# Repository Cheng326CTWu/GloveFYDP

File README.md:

# GloveFYDP

## Environment requirements
* System Workbench for STM32
* A serial terminal like CoolTerm, Putty, TeraTerm
* STMCubeMX

## Hardware requirements
* STM Nucleo board.
* Micro usb type B cable for the Nucleo.
* Peripherals used so far include the Sparkfun LSM9DS1 breakout, and the Adafruit TCA TCA9548A breakout.

## Source files
Most files were generated automatically by STMCubeMX. Src/ contains the actual source files we work on.
The STMCube project is the .ioc file.

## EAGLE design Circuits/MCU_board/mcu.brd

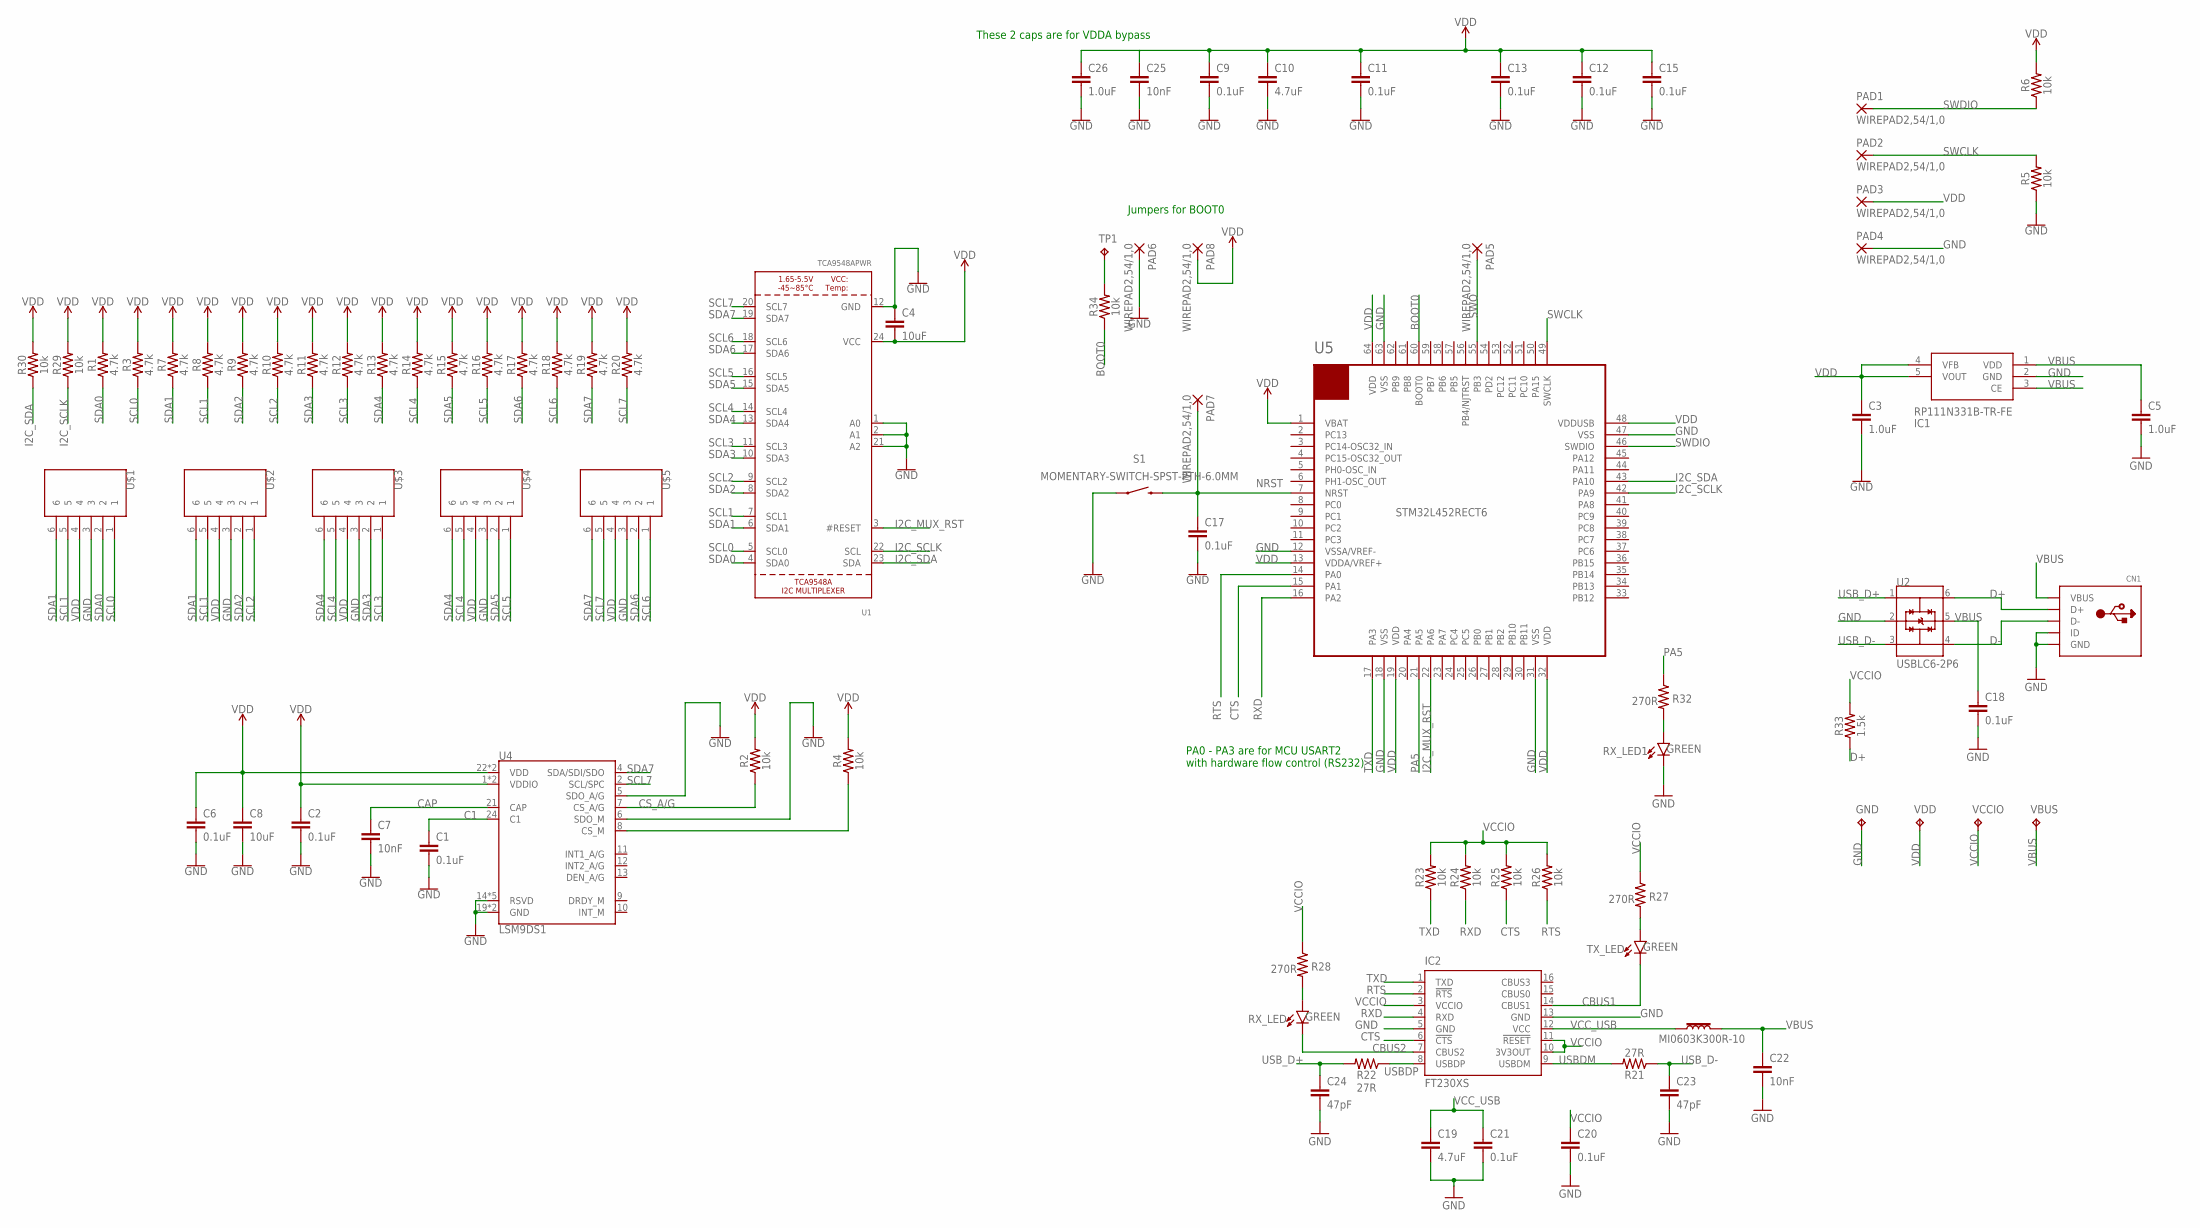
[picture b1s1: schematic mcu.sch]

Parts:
C1, C2, C6, C9, C11, C12, C13, C15, C17, C18, C20, C21: 0.1uF; 0603
C3, C5, C26: 1.0uF; 0603
C4, C8: 10uF; 0603
C7, C22, C25: 10nF; 0603
C10, C19: 4.7uF; 0603
C23, C24: 47pF; 0603
CN1: USBMINIB; USB-MINIB
GND: TPB2,54; B2,54
IC1: RP111N331B-TR-FE; SOT95P280X120-5N
IC2: FT230XS; SSOP16
MI0603K300R-10: 30Ω/1.8A; 0603
PAD1, PAD2, PAD3, PAD4, PAD5, PAD6, PAD7, PAD8: WIREPAD2,54/1,0; 2,54/1,0
R1, R3, R7, R8, R9, R10, R11, R12, R13, R14, R15, R16, R17, R18, R19, R20: 4.7k; 0603
R2, R4, R5, R6, R23, R24, R25, R26, R29, R30, R34: 10k; 0603
R21, R22: 27R; 0603
R27, R28, R32: 270R; 0603
R33: 1.5k; 0603
RX_LED, RX_LED1: GREEN; LED-0603
S1: MOMENTARY-SWITCH-SPST-PTH-6.0MM; TACTILE_SWITCH_PTH_6.0MM
TP1: TPB1,27; B1,27
TX_LED: GREEN; LED-0603
U1: TCA9548APWR; TSSOP24
U2: USBLC6-2P6; SOT50P160X60-6N
U4: LSM9DS1; LGA-24-3.5X3
U5: STM32L452RECT6; LQFP-64
U$1, U$2, U$3, U$4, U$5: MOLEX_522070633; MOLEX6_1MM
VBUS: TPB2,54; B2,54
VCCIO: TPB2,54; B2,54
VDD: TPB2,54; B2,54

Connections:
BOOT0: R34.1, U5.60 (BOOT0)
C1: C1.1, U4.24 (C1)
CAP: C7.1, U4.21 (CAP)
CBUS1: IC2.14 (CBUS1), TX_LED.C
CBUS2: IC2.7 (CBUS2), RX_LED.C
CS_A/G: R2.1, U4.7 (CS_A/G)
CS_M: R4.1, U4.8 (CS_M)
CTS: IC2.6 (!CTS), R25.1, U5.15 (PA1)
D+: CN1.D+, R33.1, U2.6 (I/O1_2)
D-: CN1.D-, U2.4 (I/O2_2)
GND: C1.2, C2.2, C3.2, C4.1, C5.2, C6.2, C7.2, C8.2, C9.2, C10.2, C11.2, C12.2, C13.2, C15.2, C17.2, C18.2, C19.2, C20.2, C21.2, C22.2, C23.2, C24.2, C25.2, C26.2, CN1.GND, CN1.ID, GND.TP, IC1.2 (GND), IC2.5 (GND), IC2.13 (GND), PAD4.1, PAD6.1, R5.1, RX_LED1.C, S1.1, U1.1 (A0), U1.2 (A1), U1.12 (GND), U1.21 (A2), U2.2 (GND), U4.5 (SDO_A/G), U4.6 (SDO_M), U4.14 (RSVD), U4.15 (RSVD), U4.16 (RSVD), U4.17 (RSVD), U4.18 (RSVD), U4.19 (GND), U4.20 (GND), U5.12 (VSSA/VREF-), U5.18 (VSS), U5.31 (VSS), U5.47 (VSS), U5.63 (VSS), U$1.3, U$2.3, U$3.3, U$4.3, U$5.3
I2C_MUX_RST: U1.3 (#RESET), U5.22 (PA6)
I2C_SCLK: R29.1, U1.22 (SCL), U5.42 (PA9)
I2C_SDA: R30.1, U1.23 (SDA), U5.43 (PA10)
unnamed: R27.2, TX_LED.A
unnamed: R28.2, RX_LED.A
unnamed: R32.2, RX_LED1.A
unnamed: R34.2, TP1.TP
NRST: C17.1, PAD7.1, S1.3 (2), U5.7 (NRST)
PA5: R32.1, U5.21 (PA5)
RTS: IC2.2 (!RTS), R26.1, U5.14 (PA0)
RXD: IC2.4 (RXD), R24.1, U5.16 (PA2)
SCL0: R3.1, U1.5 (SCL0), U$1.1
SCL1: R8.1, U1.7 (SCL1), U$1.5, U$2.5
SCL2: R10.1, U1.9 (SCL2), U$2.1
SCL3: R12.1, U1.11 (SCL3), U$3.1
SCL4: R14.1, U1.14 (SCL4), U$3.5, U$4.5
SCL5: R16.1, U1.16 (SCL5), U$4.1
SCL6: R18.1, U1.18 (SCL6), U$5.1
SCL7: R20.1, U1.20 (SCL7), U4.2 (SCL/SPC), U$5.5
SDA0: R1.1, U1.4 (SDA0), U$1.2
SDA1: R7.1, U1.6 (SDA1), U$1.6, U$2.6
SDA2: R9.1, U1.8 (SDA2), U$2.2
SDA3: R11.1, U1.10 (SDA3), U$3.2
SDA4: R13.1, U1.13 (SDA4), U$3.6, U$4.6
SDA5: R15.1, U1.15 (SDA5), U$4.2
SDA6: R17.1, U1.17 (SDA6), U$5.2
SDA7: R19.1, U1.19 (SDA7), U4.4 (SDA/SDI/SDO), U$5.6
SWCLK: PAD2.1, R5.2, U5.49 (SWCLK)
SWDIO: PAD1.1, R6.1, U5.46 (SWDIO)
SWO: PAD5.1, U5.55 (PB3)
TXD: IC2.1 (TXD), R23.1, U5.17 (PA3)
USBDM: IC2.9 (USBDM), R21.2
USBDP: IC2.8 (USBDP), R22.1
USB_D+: C24.1, R22.2, U2.1 (I/O1_1)
USB_D-: C23.1, R21.1, U2.3 (I/O2_1)
VBUS: C5.1, C18.1, C22.1, CN1.VBUS, IC1.1 (VDD), IC1.3 (CE), MI0603K300R-10.2, U2.5 (VBUS), VBUS.TP
VCCIO: C20.1, IC2.3 (VCCIO), IC2.10 (3V3OUT), IC2.11 (!RESET), R23.2, R24.2, R25.2, R26.2, R27.1, R28.1, R33.2, VCCIO.TP
VCC_USB: C19.1, C21.1, IC2.12 (VCC), MI0603K300R-10.1
VDD: C2.1, C3.1, C4.2, C6.1, C8.1, C9.1, C10.1, C11.1, C12.1, C13.1, C15.1, C25.1, C26.1, IC1.4 (VFB), IC1.5 (VOUT), PAD3.1, PAD8.1, R1.2, R2.2, R3.2, R4.2, R6.2, R7.2, R8.2, R9.2, R10.2, R11.2, R12.2, R13.2, R14.2, R15.2, R16.2, R17.2, R18.2, R19.2, R20.2, R29.2, R30.2, U1.24 (VCC), U4.1 (VDDIO), U4.3 (VDDIO), U4.22 (VDD), U4.23 (VDD), U5.1 (VBAT), U5.13 (VDDA/VREF+), U5.19 (VDD), U5.32 (VDD), U5.48 (VDDUSB), U5.64 (VDD), U$1.4, U$2.4, U$3.4, U$4.4, U$5.4, VDD.TP

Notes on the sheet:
PA0 - PA3 are for MCU USART2 with hardware flow control (RS232)
These 2 caps are for VDDA bypass
Jumpers for BOOT0

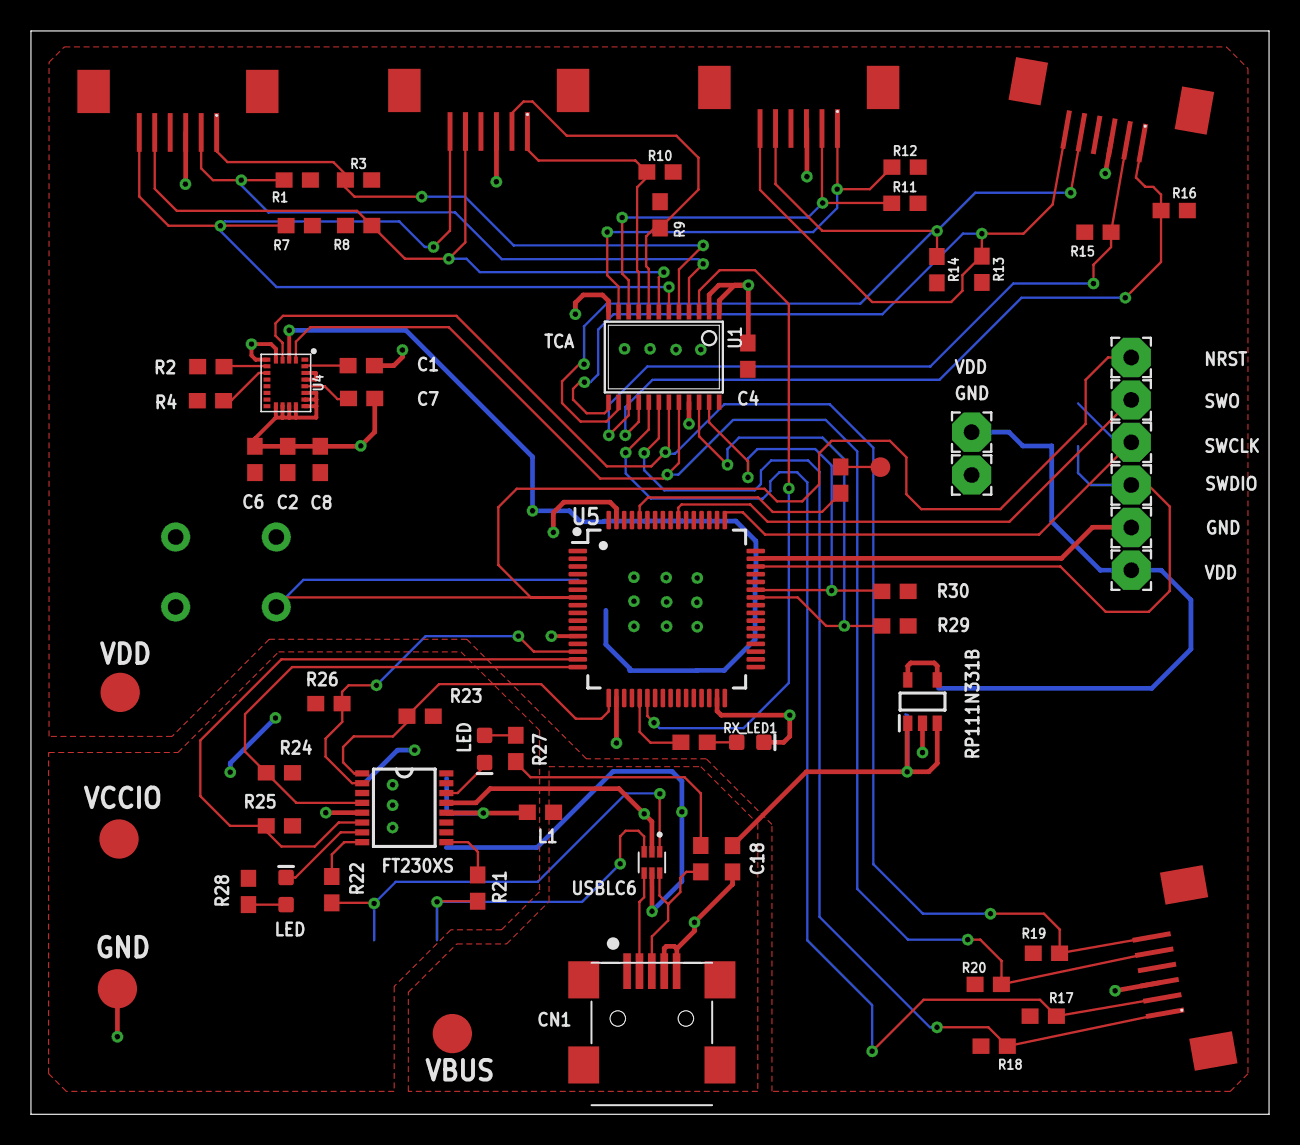
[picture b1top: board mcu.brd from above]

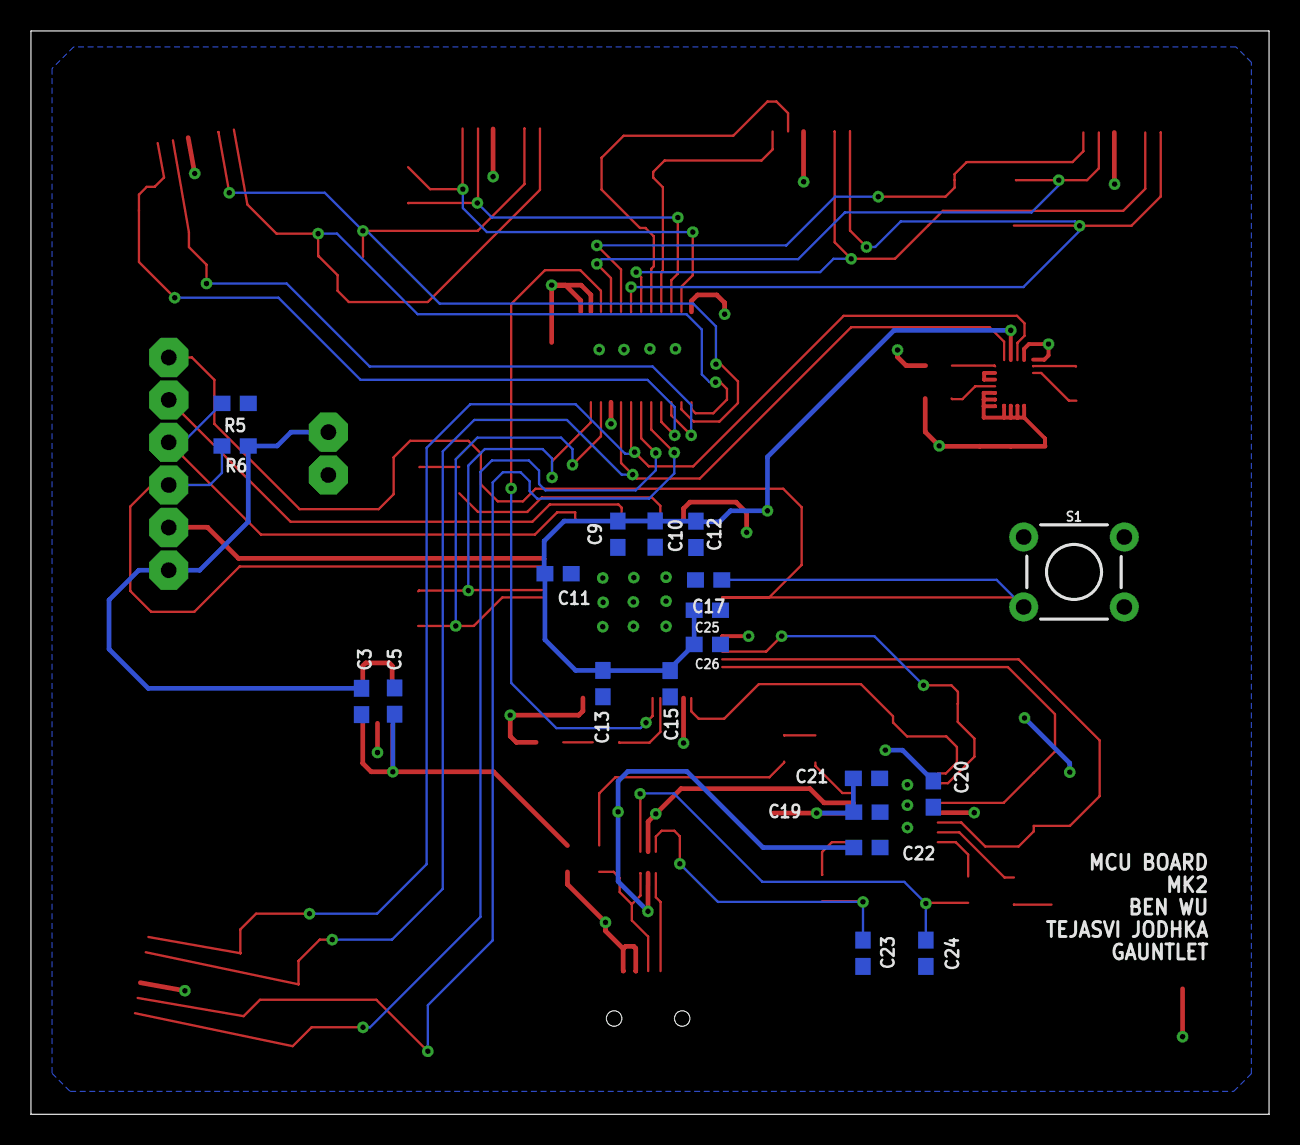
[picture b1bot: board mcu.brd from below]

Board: 2 copper layers, 80.0 x 70.0 mm, 87 parts (20 on the bottom side), 50 nets.

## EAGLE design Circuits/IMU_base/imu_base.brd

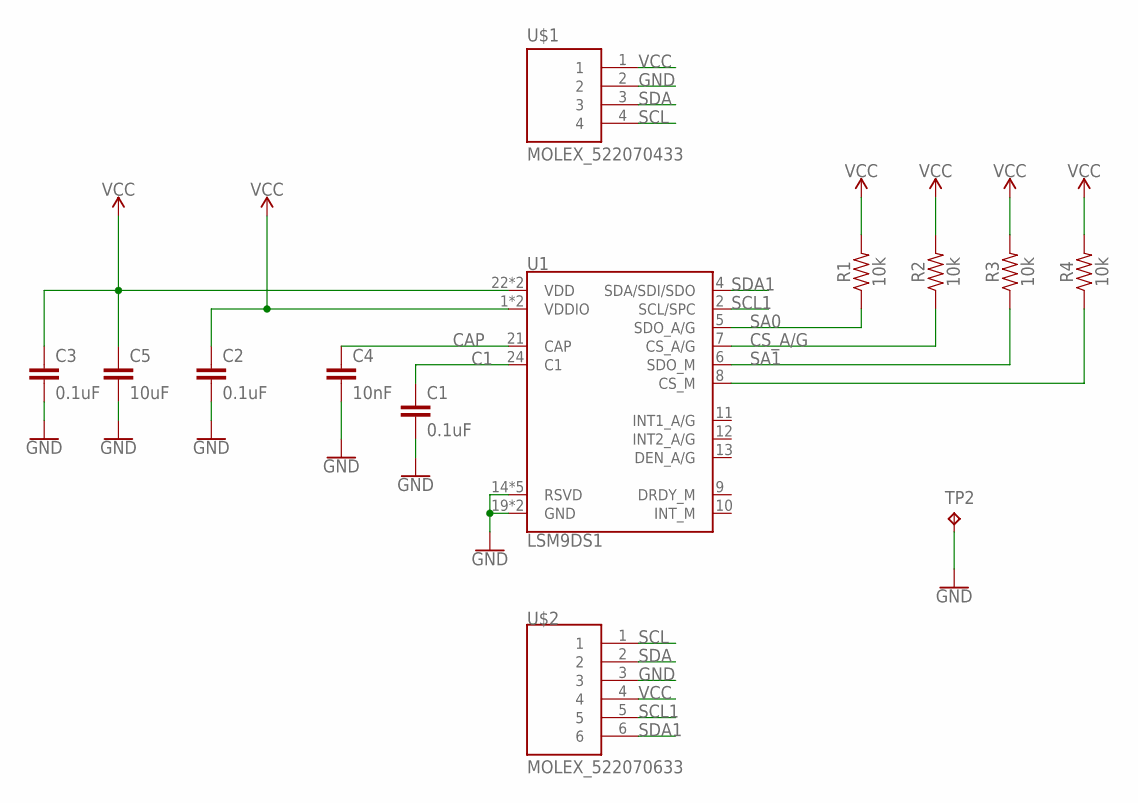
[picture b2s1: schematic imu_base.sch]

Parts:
C1, C2, C3: 0.1uF; 0603
C4: 10nF; 0603
C5: 10uF; 0603
R1, R2, R3, R4: 10k; 0603
TP2: TPB2,54; B2,54
U1: LSM9DS1; LGA-24-3.5X3
U$1: MOLEX_522070433; MOLEX4_1MM
U$2: MOLEX_522070633; MOLEX6_1MM

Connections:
C1: C1.1, U1.24 (C1)
CAP: C4.1, U1.21 (CAP)
CS_A/G: R2.1, U1.7 (CS_A/G)
CS_M: R4.1, U1.8 (CS_M)
GND: C1.2, C2.2, C3.2, C4.2, C5.2, TP2.TP, U1.14 (RSVD), U1.15 (RSVD), U1.16 (RSVD), U1.17 (RSVD), U1.18 (RSVD), U1.19 (GND), U1.20 (GND), U$1.2, U$2.3
SA0: R1.1, U1.5 (SDO_A/G)
SA1: R3.1, U1.6 (SDO_M)
SCL: U$1.4, U$2.1
SCL1: U1.2 (SCL/SPC), U$2.5
SDA: U$1.3, U$2.2
SDA1: U1.4 (SDA/SDI/SDO), U$2.6
VCC: C2.1, C3.1, C5.1, R1.2, R2.2, R3.2, R4.2, U1.1 (VDDIO), U1.3 (VDDIO), U1.22 (VDD), U1.23 (VDD), U$1.1, U$2.4

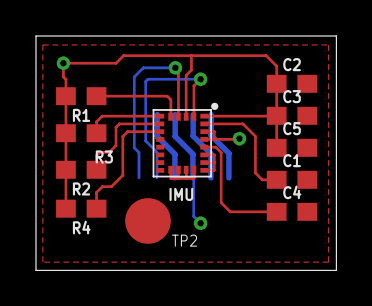
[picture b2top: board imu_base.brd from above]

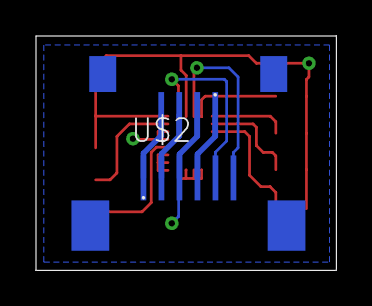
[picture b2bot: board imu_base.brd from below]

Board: 2 copper layers, 16.7 x 13.0 mm, 13 parts (2 on the bottom side), 12 nets.

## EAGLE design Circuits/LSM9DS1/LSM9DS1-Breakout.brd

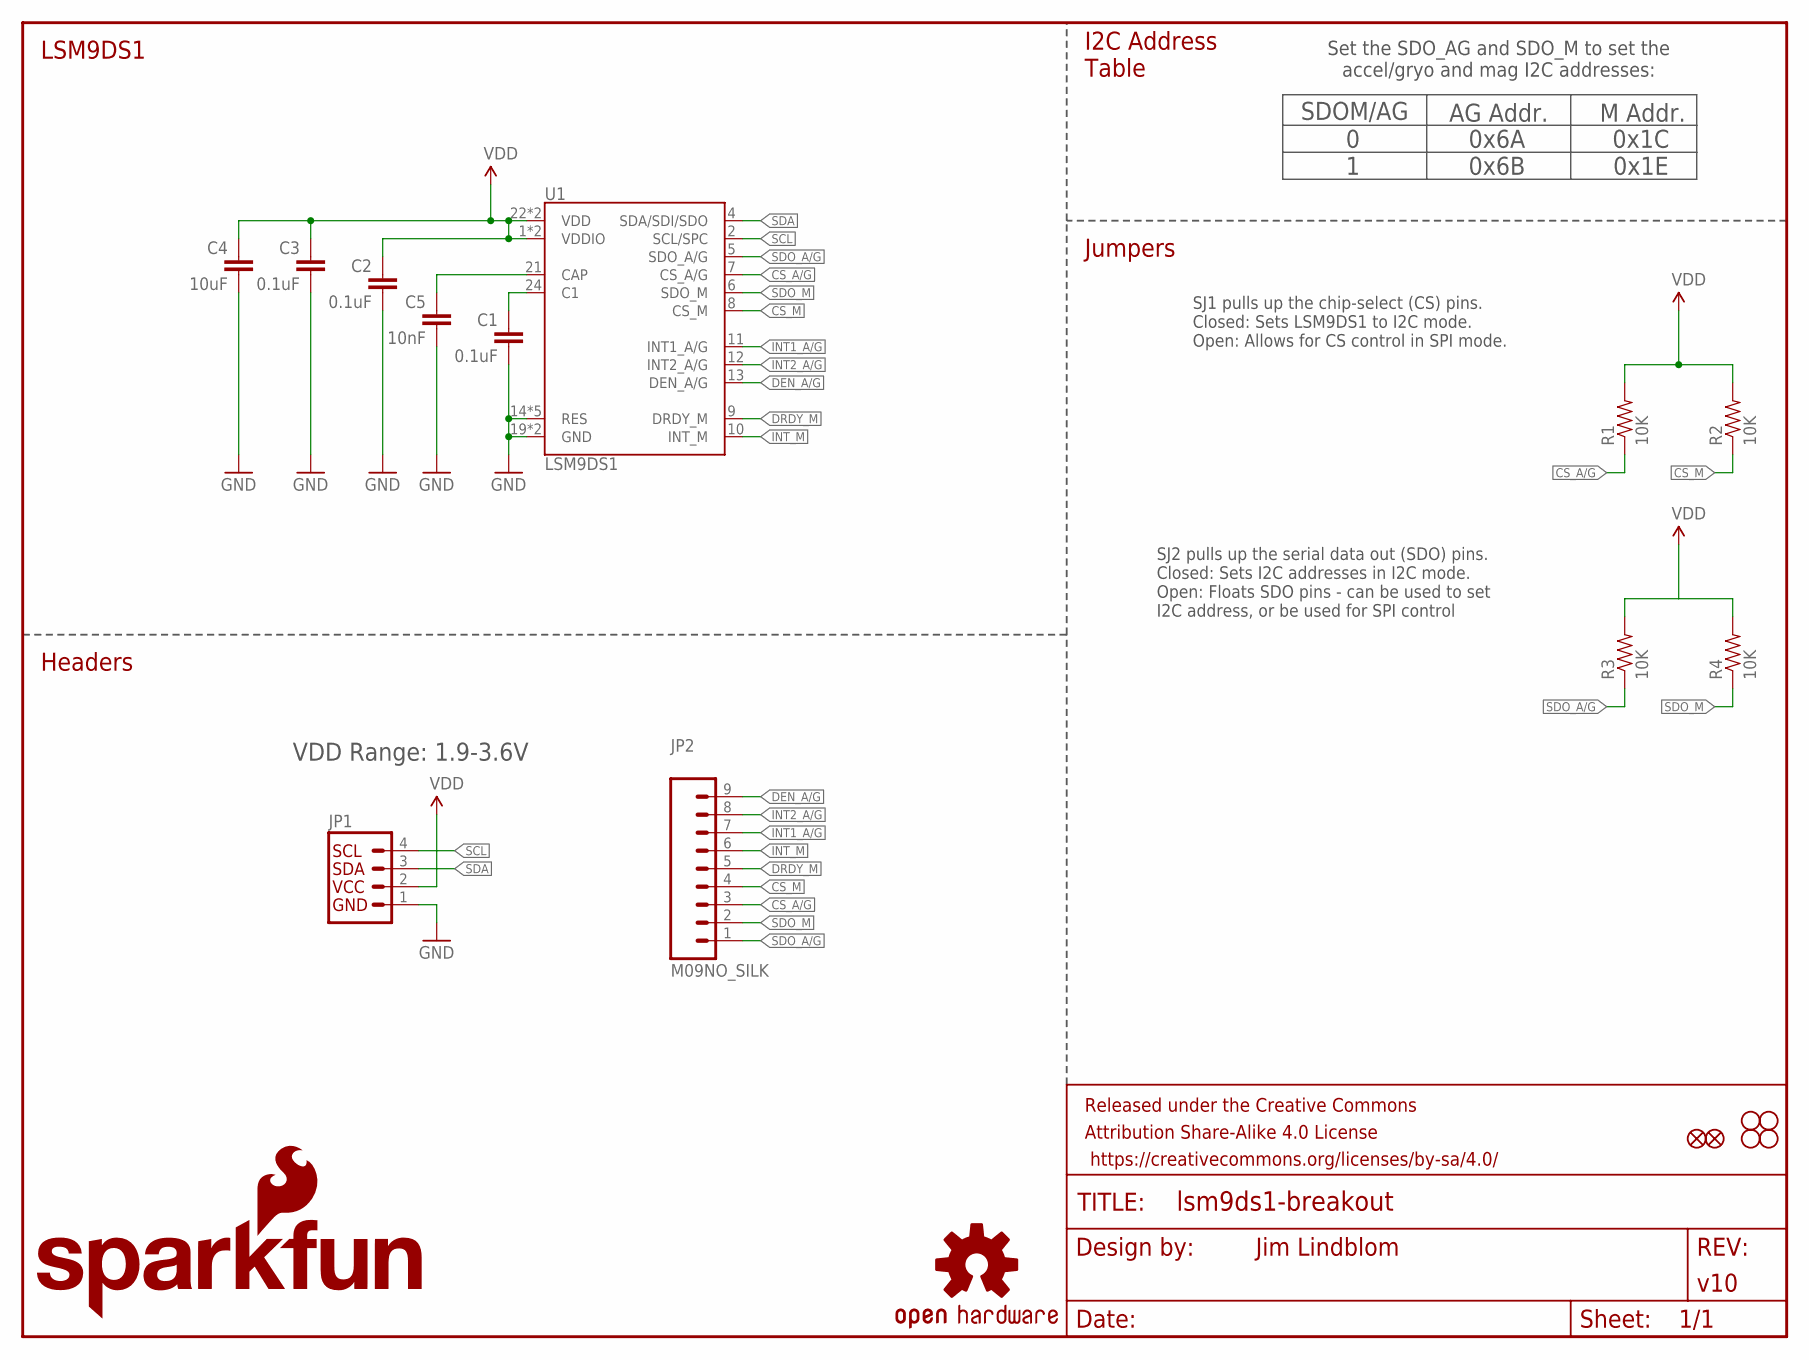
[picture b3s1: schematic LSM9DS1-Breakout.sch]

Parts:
C1, C2, C3: 0.1uF; 0603-CAP
C4: 10uF; 0603-CAP
C5: 10nF; 0603-CAP
FID1, FID2: FIDUCIAL1X2; FIDUCIAL-1X2
FRAME1: FRAME-LETTER; CREATIVE_COMMONS
JP1: I2C_STANDARD_NO_SILK; 1X04_NO_SILK
JP2: M09NO_SILK; 1X09_NO_SILK
LOGO1: SFE_LOGO_NAME.1_INCH; SFE_LOGO_NAME_.1
LOGO2: SFE_LOGO_FLAME.2_INCH; SFE_LOGO_FLAME_.2
LOGO3: OSHW-LOGOS; OSHW-LOGO-S
R1, R2, R3, R4: 10K; 0603-RES
STANDOFF1, STANDOFF2, STANDOFF3, STANDOFF4: STAND-OFF
U1: LSM9DS1; LGA24-8X4

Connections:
C1: C1.1, U1.24 (C1)
CAP: C5.1, U1.21 (CAP)
CS_A/G: JP2.3, R1.1, U1.7 (CS_A/G)
CS_M: JP2.4, R2.1, U1.8 (CS_M)
DEN_A/G: JP2.9, U1.13 (DEN_A/G)
DRDY_M: JP2.5, U1.9 (DRDY_M)
GND: C1.2, C2.2, C3.2, C4.2, C5.2, JP1.1, U1.14 (RES), U1.15 (RES), U1.16 (RES), U1.17 (RES), U1.18 (RES), U1.19 (GND), U1.20 (GND)
INT1_A/G: JP2.7, U1.11 (INT1_A/G)
INT2_A/G: JP2.8, U1.12 (INT2_A/G)
INT_M: JP2.6, U1.10 (INT_M)
SCL: JP1.4, U1.2 (SCL/SPC)
SDA: JP1.3, U1.4 (SDA/SDI/SDO)
SDO_A/G: JP2.1, R3.1, U1.5 (SDO_A/G)
SDO_M: JP2.2, R4.1, U1.6 (SDO_M)
VDD: C2.1, C3.1, C4.1, JP1.2, R1.2, R2.2, R3.2, R4.2, U1.1 (VDDIO), U1.3 (VDDIO), U1.22 (VDD), U1.23 (VDD)

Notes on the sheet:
SDOM/AG
0x1C 0x1E
AG Addr.
0 1
M Addr.
0x6A 0x6B
Set the SDO_AG and SDO_M to set the accel/gryo and mag I2C addresses:
SJ1 pulls up the chip-select (CS) pins. Closed: Sets LSM9DS1 to I2C mode. Open: Allows for CS control in SPI mode.
SJ2 pulls up the serial data out (SDO) pins. Closed: Sets I2C addresses in I2C mode. Open: Floats SDO pins - can be used to set I2C address, or be used for SPI control
Jumpers
I2C Address Table
LSM9DS1
Headers
VDD Range: 1.9-3.6V

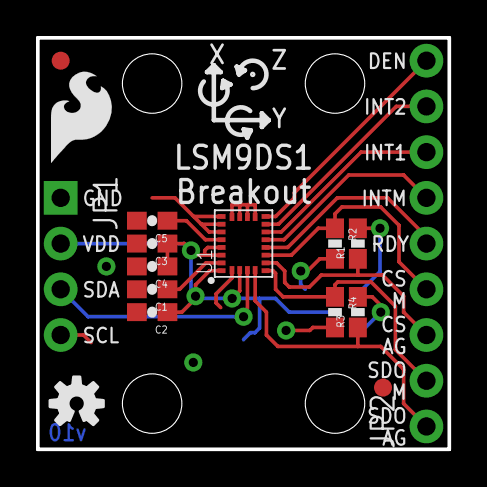
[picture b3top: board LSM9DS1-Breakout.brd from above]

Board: 2 copper layers, 22.9 x 22.9 mm, 22 parts (1 on the bottom side), 15 nets.

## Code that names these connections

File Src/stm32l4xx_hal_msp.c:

/* USER CODE BEGIN Header */
/**
  ******************************************************************************
  * File Name          : stm32l4xx_hal_msp.c
  * Description        : This file provides code for the MSP Initialization 
  *                      and de-Initialization codes.
  ******************************************************************************
  * @attention
  *
  * <h2><center>&copy; Copyright (c) 2019 STMicroelectronics.
  * All rights reserved.</center></h2>
  *
  * This software component is licensed by ST under BSD 3-Clause license,
  * the "License"; You may not use this file except in compliance with the
  * License. You may obtain a copy of the License at:
  *                        opensource.org/licenses/BSD-3-Clause
  *
  ******************************************************************************
  */
/* USER CODE END Header */

/* Includes ------------------------------------------------------------------*/
#include "main.h"
/* USER CODE BEGIN Includes */

/* USER CODE END Includes */
extern DMA_HandleTypeDef hdma_usart2_rx;

extern DMA_HandleTypeDef hdma_usart2_tx;

/* Private typedef -----------------------------------------------------------*/
/* USER CODE BEGIN TD */

/* USER CODE END TD */

/* Private define ------------------------------------------------------------*/
/* USER CODE BEGIN Define */
 
/* USER CODE END Define */

/* Private macro -------------------------------------------------------------*/
/* USER CODE BEGIN Macro */

/* USER CODE END Macro */

/* Private variables ---------------------------------------------------------*/
/* USER CODE BEGIN PV */

/* USER CODE END PV */

/* Private function prototypes -----------------------------------------------*/
/* USER CODE BEGIN PFP */

/* USER CODE END PFP */

/* External functions --------------------------------------------------------*/
/* USER CODE BEGIN ExternalFunctions */

/* USER CODE END ExternalFunctions */

/* USER CODE BEGIN 0 */

/* USER CODE END 0 */
/**
  * Initializes the Global MSP.
  */
void HAL_MspInit(void)
{
  /* USER CODE BEGIN MspInit 0 */

  /* USER CODE END MspInit 0 */

  __HAL_RCC_SYSCFG_CLK_ENABLE();
  __HAL_RCC_PWR_CLK_ENABLE();

  /* System interrupt init*/

  /* USER CODE BEGIN MspInit 1 */

  /* USER CODE END MspInit 1 */
}

/**
* @brief I2C MSP Initialization
* This function configures the hardware resources used in this example
* @param hi2c: I2C handle pointer
* @retval None
*/
void HAL_I2C_MspInit(I2C_HandleTypeDef* hi2c)
{
  GPIO_InitTypeDef GPIO_InitStruct = {0};
  if(hi2c->Instance==I2C1)
  {
  /* USER CODE BEGIN I2C1_MspInit 0 */

  /* USER CODE END I2C1_MspInit 0 */
  
    __HAL_RCC_GPIOA_CLK_ENABLE();
    /**I2C1 GPIO Configuration    
    PA9     ------> I2C1_SCL
    PA10     ------> I2C1_SDA 
    */
    GPIO_InitStruct.Pin = GPIO_PIN_9|GPIO_PIN_10;
    GPIO_InitStruct.Mode = GPIO_MODE_AF_OD;
    GPIO_InitStruct.Pull = GPIO_PULLUP;
    GPIO_InitStruct.Speed = GPIO_SPEED_FREQ_VERY_HIGH;
    GPIO_InitStruct.Alternate = GPIO_AF4_I2C1;
    HAL_GPIO_Init(GPIOA, &GPIO_InitStruct);

    /* Peripheral clock enable */
    __HAL_RCC_I2C1_CLK_ENABLE();
  /* USER CODE BEGIN I2C1_MspInit 1 */

  /* USER CODE END I2C1_MspInit 1 */
  }

}

/**
* @brief I2C MSP De-Initialization
* This function freeze the hardware resources used in this example
* @param hi2c: I2C handle pointer
* @retval None
*/
void HAL_I2C_MspDeInit(I2C_HandleTypeDef* hi2c)
{
  if(hi2c->Instance==I2C1)
  {
  /* USER CODE BEGIN I2C1_MspDeInit 0 */

  /* USER CODE END I2C1_MspDeInit 0 */
    /* Peripheral clock disable */
    __HAL_RCC_I2C1_CLK_DISABLE();
  
    /**I2C1 GPIO Configuration    
    PA9     ------> I2C1_SCL
    PA10     ------> I2C1_SDA 
    */
    HAL_GPIO_DeInit(GPIOA, GPIO_PIN_9|GPIO_PIN_10);

  /* USER CODE BEGIN I2C1_MspDeInit 1 */

  /* USER CODE END I2C1_MspDeInit 1 */
  }

}

/**
* @brief UART MSP Initialization
* This function configures the hardware resources used in this example
* @param huart: UART handle pointer
* @retval None
*/
void HAL_UART_MspInit(UART_HandleTypeDef* huart)
{
  GPIO_InitTypeDef GPIO_InitStruct = {0};
  if(huart->Instance==USART2)
  {
  /* USER CODE BEGIN USART2_MspInit 0 */

  /* USER CODE END USART2_MspInit 0 */
    /* Peripheral clock enable */
    __HAL_RCC_USART2_CLK_ENABLE();
  
    __HAL_RCC_GPIOA_CLK_ENABLE();
    /**USART2 GPIO Configuration    
    PA0     ------> USART2_CTS
    PA1     ------> USART2_RTS
    PA2     ------> USART2_TX
    PA3     ------> USART2_RX 
    */
    GPIO_InitStruct.Pin = GPIO_PIN_0|GPIO_PIN_1|USART_TX_Pin|USART_RX_Pin;
    GPIO_InitStruct.Mode = GPIO_MODE_AF_PP;
    GPIO_InitStruct.Pull = GPIO_NOPULL;
    GPIO_InitStruct.Speed = GPIO_SPEED_FREQ_VERY_HIGH;
    GPIO_InitStruct.Alternate = GPIO_AF7_USART2;
    HAL_GPIO_Init(GPIOA, &GPIO_InitStruct);

    /* USART2 DMA Init */
    /* USART2_RX Init */
    hdma_usart2_rx.Instance = DMA1_Channel6;
    hdma_usart2_rx.Init.Request = DMA_REQUEST_2;
    hdma_usart2_rx.Init.Direction = DMA_PERIPH_TO_MEMORY;
    hdma_usart2_rx.Init.PeriphInc = DMA_PINC_DISABLE;
    hdma_usart2_rx.Init.MemInc = DMA_MINC_ENABLE;
    hdma_usart2_rx.Init.PeriphDataAlignment = DMA_PDATAALIGN_BYTE;
    hdma_usart2_rx.Init.MemDataAlignment = DMA_MDATAALIGN_BYTE;
    hdma_usart2_rx.Init.Mode = DMA_NORMAL;
    hdma_usart2_rx.Init.Priority = DMA_PRIORITY_LOW;
    if (HAL_DMA_Init(&hdma_usart2_rx) != HAL_OK)
    {
      Error_Handler();
    }

    __HAL_LINKDMA(huart,hdmarx,hdma_usart2_rx);

    /* USART2_TX Init */
    hdma_usart2_tx.Instance = DMA1_Channel7;
    hdma_usart2_tx.Init.Request = DMA_REQUEST_2;
    hdma_usart2_tx.Init.Direction = DMA_MEMORY_TO_PERIPH;
    hdma_usart2_tx.Init.PeriphInc = DMA_PINC_DISABLE;
    hdma_usart2_tx.Init.MemInc = DMA_MINC_ENABLE;
    hdma_usart2_tx.Init.PeriphDataAlignment = DMA_PDATAALIGN_BYTE;
    hdma_usart2_tx.Init.MemDataAlignment = DMA_MDATAALIGN_BYTE;
    hdma_usart2_tx.Init.Mode = DMA_NORMAL;
    hdma_usart2_tx.Init.Priority = DMA_PRIORITY_LOW;
    if (HAL_DMA_Init(&hdma_usart2_tx) != HAL_OK)
    {
      Error_Handler();
    }

    __HAL_LINKDMA(huart,hdmatx,hdma_usart2_tx);

  /* USER CODE BEGIN USART2_MspInit 1 */

  /* USER CODE END USART2_MspInit 1 */
  }

}

/**
* @brief UART MSP De-Initialization
* This function freeze the hardware resources used in this example
* @param huart: UART handle pointer
* @retval None
*/
void HAL_UART_MspDeInit(UART_HandleTypeDef* huart)
{
  if(huart->Instance==USART2)
  {
  /* USER CODE BEGIN USART2_MspDeInit 0 */

  /* USER CODE END USART2_MspDeInit 0 */
    /* Peripheral clock disable */
    __HAL_RCC_USART2_CLK_DISABLE();
  
    /**USART2 GPIO Configuration    
    PA0     ------> USART2_CTS
    PA1     ------> USART2_RTS
    PA2     ------> USART2_TX
    PA3     ------> USART2_RX 
    */
    HAL_GPIO_DeInit(GPIOA, GPIO_PIN_0|GPIO_PIN_1|USART_TX_Pin|USART_RX_Pin);

    /* USART2 DMA DeInit */
    HAL_DMA_DeInit(huart->hdmarx);
    HAL_DMA_DeInit(huart->hdmatx);
  /* USER CODE BEGIN USART2_MspDeInit 1 */

  /* USER CODE END USART2_MspDeInit 1 */
  }

}

/* USER CODE BEGIN 1 */

/* USER CODE END 1 */

/************************ (C) COPYRIGHT STMicroelectronics *****END OF FILE****/

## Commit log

2019-05-13 Add project files initial
2019-05-13 Add some more project files, update readme
2019-05-20 Add sensor data scaling
2019-05-21 Add build files
2019-05-21 Add linker file
2019-05-27 Added functioning logger source and header file
2019-06-22 Add state machine
2019-06-29 Fix state transitions for idle state
2019-06-29 Update some debug files
2019-06-30 Add FIFO implementation + tests
2019-06-30 Add scheduler
2019-06-30 Change baud rate to 1 MB/s for fast data transfer
2019-06-30 More merge conflict fixing
2019-06-30 Integration of scheduler into the system.
    * Added TCA driver module
    * Added Serial communication module
    * Added scheduler tasks file
    * Changed main() to call SM_Tick and Sheduler_Tick continually
2019-07-01 Make serial work in under 40 ms / sensor packet. Numerous changes to scheduler, queue, serial interface. Added python script for serial testing
2019-07-09 Update gitignore for Eagle files
2019-07-09 Add circuits folder, containing IMU schematic+board, and design document schematics
2019-07-10 Update board/schematic/custom library with 1 mm pitch connector
2019-07-10 Remove connector silkscreen
2019-07-10 Remove silkscreen outline
2019-07-10 Silkscreen layer changes
2019-07-20 USB serial driver code - initial push
2019-07-25 Sensor fusion scripting
    * Fix numerous problems with LSM9DS1 driver
    * Add functionality to serial_test.py to make it read data, scale, and use madgwick algorithm, and plot.
    * A few minor changes to c# files, which resulted in several build file changes...
2019-10-02 Reorganize circuits files
2019-10-02 ghetto board design
2019-10-09 Add IMU base
2019-10-09 6 cond connector package with a rect outline to approx real connect placement
2019-10-13 connected 6 conn package and symbol, base board layout complete
2019-10-27 Changed LDO to LM1117 SOT223
2019-11-11 Bypass capacitors updated
2019-12-10 Added testpad in schematic and board layout to allow address to be pulled up or down when needed
2019-12-10 change test pad size up
2019-12-17 MCU changes
2019-12-17 asdf
2019-12-17 Change connector orientation so less confusion occurs
2019-12-17 Add connectors on mcu board
2019-12-17 Add SWD and reset to MCU board
2019-12-17 Add I2C mux reset GPIO
2019-12-17 set I2C lines for IMU on mcu board
2019-12-17 LDO library part
2019-12-17 Added LDO part in schematic
2019-12-18 Added LDO and fixed TVS diode connection
2019-12-19 Changed all VCC to VDD, Fixed i2c bus issue for board IMU and baseboard IMU
2019-12-19 Add IMU layout description
2019-12-19 Added i2c resistors - pulled high, Fixed capacitor package size, moved schematics around to be more organized
2019-12-24 Add FTDI chip to MCU board
2019-12-24 Fix resistors in FTDI
2019-12-25 Moved and grouped all components into board area, measured maximum board area
2019-12-26 Fixed connector mistakes, preliminary placement of all components
2019-12-27 Changed location of components
2019-12-27 FTDI preliminary routing
2019-12-27 Last imu preliminary routing
2019-12-27 repushing imu changes
2019-12-27 Moved connectors to top layer, fixed connector signals
2019-12-29 Finished first draft routing
2019-12-29 Made any power and ground traces 10 or 12 mil for more current tolerance
2019-12-29 Approved clearance issue from USB TVS diode
2019-12-29 Added thermal vias (not really sure if necessary)
2019-12-30 Add pullups for MCU I2C lines
2020-01-02 Change diode routing
2020-01-03 Moved FTDI and re-routed, Added VCCIO plane and shrunk VDD plane, Added VDD and GND Test Point
2020-01-06 Revert "Moved FTDI and re-routed, Added VCCIO plane and shrunk VDD plane, Added VDD and GND Test Point"
    This reverts commit a39282d0876712c586134e04e0ec14b12e122efb.
2020-01-07 Changed routing on FTDI, Added Testpads for each plane, Changed some connector traces
2020-01-07 Separate a couple of MCU traces to use separate vias to avoid potential loop
2020-01-07 Fixed silkscreen of components, Changed VCCIO plane
2020-01-08 Add silkscreen component names
2020-01-08 Moved connector resistor silkscreens to layer 21
2020-01-13 Add Hand model in firmware
2020-01-15 Iteration 2 of MCU board * Change decoupling caps * Power all VDD and VSS pins * Add LED to GPIO * Add Pullup to USB D+ * Add jumpers for BOOT0
2020-01-15 Changed boot0 to testpad, routed all newly added components
2020-01-15 Add headers for NRST and SWO
2020-01-15 Routed SWO and NRST pin out
2020-01-15 Add silkscreen labels for NRST and SWO
2020-01-15 Add silkscreen labels for VDD and GND headers
2020-01-16 Minor changes in firmware
2020-01-16 Fix issue with not setting 'imu' field of finger array elements
2020-01-16 Add hex file to git
2020-01-16 Change all our firmware to blinky
2020-01-16 Blinky
2020-01-16 Comment out blinky
2020-01-16 Enable hw flow control for RS232
2020-01-16 Add hex file for previous commit
2020-01-16 loop hello world
2020-01-16 Change baud rate back to 115200
2020-01-16 Change baud rate to 1200
2020-01-16 Remove uart flow control in fw
2020-01-16 Change default baud to 115200
2020-01-16 Add hex file for prev commit
2020-01-16 Swap RXD and TXD
2020-01-16 Don't swap tx/rx
2020-01-16 Add delay to hello world loop
2020-01-16 Re-enable tx/rx swap on uart
2020-01-16 Add echo test
2020-01-17 Hand array change for testing
2020-01-17 Add index finger IMUs to hand for testing
2020-01-17 Add middle finger
2020-01-17 Add pinky, ring, and thumb fingers
2020-01-17 Remove thumb and pinky
2020-01-17 Changed RTS/CTS and TXD/RXD schematic and board routing to criss-cross
2020-01-17 Test on-board IMU
2020-01-17 Add all fingers + middle of board
2020-01-18 Add all the fingers
2020-01-19 Disable printf during continuous read
2020-01-19 Fix previous commit
2020-01-19 Fix disabling of printfs
2020-01-19 Remove printf loop from main
2020-01-19 Remove some printfs
2020-01-19 Enable continuous read by default
2020-01-19 Disable printf after init
2020-01-19 Change data format
2020-01-19 Fix output data format over serial
2020-01-21 Add hex dump
2020-01-21 Go back to normal firmware
2020-01-22 Change I2c to 400 kHz, uart baud rate to 1152000
2020-01-22 Run 20 reads for profiling
2020-01-22 Improve debug msg
2020-01-22 Change back to 115200
2020-01-22 Change back to 1152000
2020-01-22 Change back to continuous read
2020-02-01 Increase ODR to 119 Hz for A/G, 80 Hz for mag. Also remove compiler warnings
2020-03-08 Serial test script updates + baud rate back to 1152000
2020-03-12 update serial script
2020-03-12 Re-create file at beginning
2020-03-12 Change prints
2020-03-12 Dump data
2020-03-12 Slow down
2020-03-12 back to 1152000
2020-03-12 Change speed to 576000
2020-03-12 back to 115200
2020-03-13 go back to nucleo
2020-03-13 Switch to 1 finger

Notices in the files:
parts and their libraries:
SparkFun-Capacitors: Licensing: Creative Commons ShareAlike 4.0 International - https://creativecommons.org/licenses/by-sa/4.0
SparkFun-Aesthetics: Released under the Creative Commons Attribution Share-Alike 4.0 License
SparkFun-Aesthetics: https://creativecommons.org/licenses/by-sa/4.0
